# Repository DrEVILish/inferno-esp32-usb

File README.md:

# inferno-esp32-usb

Fixed-function 32×32 audio bridge: Inferno-compatible AoIP on RJ45 ↔ USB Audio Class 2.0 on USB-C. One ESP32-P4, no settings, boots and runs.

- **Network side:** AoIP device speaking the Dante-compatible protocol as implemented by [Inferno](https://github.com/teodly/inferno). 32 transmit + 32 receive channels, 48 kHz, 24-bit.
- **USB side:** class-compliant USB Audio Class 2.0 device. 32 playback + 32 capture channels, 48 kHz, High-Speed asynchronous with explicit feedback.
- **Mapping (fixed 1:1):** USB playback N → network TX N, network RX N → USB capture N.
- **Operation:** no configuration UI. Boots on USB-C bus power and runs (PoE deferred).

Target SoC: **ESP32-P4** — the only ESP32 with High-Speed USB (32×32 needs it; the S3's Full-Speed port tops out around 2–4 channels) plus an Ethernet MAC with IEEE 1588 hardware timestamps.

> Status: firmware for milestones M1–M5 is written but **not yet run on hardware** (2026-10-13). Until the bench matrix (docs/20/21) has passed, USB enumeration/throughput, Ethernet/PTP behaviour and the real-time figures quoted in the docs are **claims, not measurements** — do not rely on them. Next steps are bench order, own board, and open questions in `docs/30-roadmap.md`. Not affiliated with or endorsed by any AoIP protocol vendor.

**Threat model:** this is a dissector of an unauthenticated Dante-class
protocol on a LAN. The control plane (ARC/CMC/flow-control, ports 4440/8800/4455)
and info multicast accept any host: basic sanity (destination checks,
rate limits, name validation) is enforced, and abuse is counted in telemetry
(`aoip_info_drops`, `ptp_hw_*`, …), but there is no authentication — as with
Dante/Inferno itself. A hostile host on the same segment can re-route RX
channels, rename every channel, create or stop TX flows, and keep the
control task busy; info multicast is bounded by a token bucket and
degraded-startup state is visible in telemetry (`aoip_start_degraded`).
Assign it a port on a managed switch with ACLs / IGMP snooping, never a
flat, hostile network; if hostile LANs are actually in scope, an
authentication layer would have to be added on top (protocol-divergent).

Dev board: **Waveshare ESP32-P4-ETH** (RJ45/IP101; HS USB OTG on its 4-pin header → USB-C pigtail).

## Repo layout

| path | what |
|---|---|
| `firmware/` | ESP-IDF v6.1 firmware (C). See table below |
| `docs/` | Design notes, bench procedure, roadmap. See index below |
| `hardware/` | Own rev-1 board: SKiDL schematic-as-code → KiCad PCB (placement done, not routed) |
| `tools/` | Build scripts, host test/probe tools, simulations, host test runner |
| `patches/` | `esp_eth-rx64.patch`: raises IDF v6.1 EMAC RX ring cap 30 → 64 |
| `third_party/` | **Reference clones, study only, never committed** (see `.gitignore`): `inferno-esp32-p4` (8-ch RX-only prior art) and `inferno-upstream` (protocol reference) |
| `CHANGELOG.md` | Change log of the post-import work (releases 0.1.0/0.1.1) |

## Firmware

`firmware/` (ESP-IDF v6.1, C, GPL-3.0-or-later):

| part | files | doc |
|---|---|---|
| shared rings, config, telemetry | `main/audio`, `main/app_config.h`, `main/sys` | `docs/01-architecture.md` |
| Ethernet fast path, 1588 media clock, PTPv1 follower | `main/net`, `main/clock` | `docs/11-net-clock.md` |
| USB Audio 2.0, 32×32 HS async, own class driver on TinyUSB | `main/usb` | `docs/10-usb.md` |
| AoIP (Inferno-compatible): mDNS, ARC, CMC, info, flows TX/RX, subscriptions | `main/aoip` | `docs/12-aoip.md` |

Design details: single 1588 time base slaved to the PTPv1 leader; media clock derived arithmetically (no ASRC, bit-transparent). Network TX is 4×8-channel flows; USB uses 896-byte packets (6+1 frames) with a 4-byte feedback endpoint every 1 ms. IDF's `esp_eth` is overridden locally (`firmware/components/esp_eth` + `patches/` + `tools/esp_eth_override.sh`) for a 64-descriptor RX ring and hold-not-flush DMA behavior.

## Docs index

| doc | contents |
|---|---|
| `docs/00-plan.md` | Goal, starting points, milestones M0–M8, risks, open questions |
| `docs/01-architecture.md` | System design: clock architecture, bandwidth budgets |
| `docs/10-usb.md` | UAC2 32×32 HS async driver, descriptors, feedback engine, sim results |
| `docs/11-net-clock.md` | EMAC fast path, 1588 media clock, PTPv1 follower + servo |
| `docs/12-aoip.md` | AoIP module: ports, flows, subscriptions, NVS persistence |
| `docs/13-review-2026-10-13.md` | Cross-module review fixes (IRAM, NVS, rings, latency profiles) |
| `docs/14-latency.md` | Latency budget and profiles (10/6/4/2 ms) |
| `docs/15-profile.md` | Performance instrumentation, hot-path probes, gated optimization backlog |
| `docs/20-bench-testing.md` | Bench setup and test sequence (M1–M8) |
| `docs/21-latency-matrix.md` | Round-trip test matrix: 10/6/4/2 ms × 32/16/8/4/2 ch, modes A/B/C |
| `docs/30-roadmap.md` | Roadmap: no-HW phase, bench order, own board, release |
| `docs/40-board-rev1.md` | Own board rev 1: rationale, values, pins, power, risks |

## Hardware

`hardware/` holds the custom rev-1 board: USB-C (UAC2 HS, bus-powered) + RJ45 (10/100 RMII) on an ESP32-P4NRW32X, SKiDL schematic (`usb_inferno.py`) generating the KiCad netlist, BOM (`bom.csv`), and placed-but-unrouted 4-layer PCB. Full story in `hardware/README.md` and `docs/40-board-rev1.md`. Regenerate with `hardware/build.sh` (needs KiCad 9 + SKiDL venv); once human routing starts, stop regenerating the PCB and import netlist changes in pcbnew instead.

## Build

Prerequisites: ESP-IDF v6.1 with tools installed. `tools/idf-env.sh` sources it from `/opt/toolchain` — adjust the paths there if your IDF lives elsewhere.

```sh
tools/build.sh                         # production build (ends with check_iram.py)
tools/build-variant.sh USB_LOOPBACK    # bench variants: USB_LOOPBACK | NET_LOOPBACK | TONE
tools/build-matrix.sh                  # latency/channel test images (see docs/21-latency-matrix.md)
```

Every build ends with `tools/check_iram.py`: everything the USB interrupt can reach must be IRAM-resident (flash writes disable the cache). A failure fails the build.

Flash (example): `. tools/idf-env.sh && cd firmware && idf.py -p /dev/ttyACM0 flash`.

## Bench testing

Firmware written ≠ firmware proven. Start at `docs/20-bench-testing.md`: Waveshare board + managed switch with a Dante leader + Inferno on Linux, USB HS pigtail, telemetry over UDP (port 7779 via `tools/net_stats.py`).

| tool | purpose |
|---|---|
| `tools/build-variant.sh`, `tools/build-matrix.sh` | test images (loopback/tone, latency×channel matrix) |
| `tools/usb_loopback_test.py`, `tools/usb_descriptor_check.py` | M1: enumeration, 896 B packets, bit-exact OUT→IN |
| `tools/net_stats.py` | UDP telemetry receiver |
| `tools/aoip_probe.py`, `tools/aoip_pcap.py` | M3–M5: discovery/control probing, packet capture analysis |
| `tools/usb_engine_sim.sh`, `tools/ptp_servo_sim.c` | host-side simulations (feedback engine, servo) |
| `tools/latency_matrix.py` | latency model behind `docs/14` and `docs/21` |
| `tools/host_tests.sh` | run every host test (fpp select, perf windows, ts split, group bitmap, fork-comparable ARC/info replies) |

## Attribution and license

- Protocol reference: [teodly/inferno](https://github.com/teodly/inferno) (Rust, GPL-3.0+/AGPL-3.0+).
- Prior art consulted: `Nickster90s/Inferno-ESP32-P4` (8-ch receive-only; **no licence file — study material only**). It lives under `third_party/` and is excluded from version control by `.gitignore`, as is `third_party/inferno-upstream`.
- Firmware in this repo is written as GPL-3.0-or-later (see `tools/check_iram.py` SPDX header and `firmware/` notes). There is not yet a top-level `LICENSE` file; adding the GPL-3.0-or-later text is an open release task (Phase D in `docs/30-roadmap.md`).
- This project is not affiliated with or endorsed by any AoIP protocol vendor.

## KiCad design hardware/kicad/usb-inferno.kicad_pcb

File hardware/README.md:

# usb-inferno hardware (rev 1)

This folder holds the custom board: USB-C (UAC2 HS, bus powered) and RJ45 (10/100
RMII) on an ESP32-P4NRW32X. The design rationale, the sources of every value, the pin
table, the power budget and the risk list are in
[`docs/40-board-rev1.md`](../docs/40-board-rev1.md).

## Layout

| path | what | generated by |
|---|---|---|
| `usb_inferno.py` | **the schematic** (SKiDL). Every part, net and BOM field | hand-written |
| `lib/gen_lib.py` | custom symbols and footprint: ESP32-P4NRW32X (QFN104), IP101GRI, TPS25200DRV | hand-written |
| `lib/usb_inferno.kicad_sym`, `lib/usb_inferno.pretty/` | KiCad library used by the netlist and the PCB | `lib/gen_lib.py` |
| `kicad/usb-inferno.net` | KiCad netlist | `usb_inferno.py` |
| `bom.csv` | grouped BOM (ref, value, description, MPN, manufacturer, LCSC, LCSC status, footprint, qty, DNP) | `usb_inferno.py` |
| `erc.log` | SKiDL ERC result | `build.sh` |
| `kicad/usb-inferno.kicad_pcb` | 4-layer board: outline, stackup, placed parts, GND/3V3 zones, not routed | `tools/make_pcb.py` |
| `kicad/usb-inferno.kicad_pro`, `.kicad_dru` | net classes and patterns, JLC minimums, custom diff-pair/length rules | `tools/make_pcb.py` |
| `kicad/drc-unrouted.rpt` | `kicad-cli pcb drc` of the unrouted board | `build.sh` |
| `tools/pin_table.py` | prints the U1/U6 pin tables in docs/40 §5 from the netlist | — |

## Regenerate (netlist → PCB)

```sh
# one-time setup (Debian 13): KiCad 9 + libraries, SKiDL in a venv
nice apt-get install -y --no-install-recommends kicad kicad-symbols kicad-footprints
python3 -m venv /opt/usb-inferno/work/venv-hw && /opt/usb-inferno/work/venv-hw/bin/pip install skidl
# KiCad global library tables (normally created by KiCad's first-run wizard):
mkdir -p ~/.config/kicad/9.0 && cp -n /usr/share/kicad/template/*-lib-table ~/.config/kicad/9.0/

hardware/build.sh        # gen_lib -> SKiDL (ERC, netlist, BOM) -> pcbnew placement -> DRC
```

`tools/make_pcb.py` **overwrites** `usb-inferno.kicad_pcb`. Once the human layout pass
starts, stop running it. Push schematic changes into the routed board with
pcbnew *File → Import Netlist* (`kicad/usb-inferno.net`, match by reference).

## Status

- **ERC (SKiDL):** 0 errors, 0 warnings. SKiDL emits a netlist, not a `.kicad_sch`, so
  KiCad's schematic ERC does not apply. The remaining "fp-lib-table not found"
  messages come from SKiDL probing for KiCad 6/7/8/10 configurations and are harmless.
- **PCB DRC (unrouted):** 0 clearance, courtyard or edge errors. All violations left
  are expected for an unrouted board: unconnected items, silk overlaps of the staged
  passives, and the REF_CLK length rule (no tracks yet).
- **Routing: not started.** See docs/40 §18 for the list of what remains.

## Verified vs assumed

Verified against a cited document during this pass:
- P4 pins, power domains, rail ranges, decoupling, the v3.x pin 54 / DCDC / DP
  changes, strapping, CHIP_PU timing, flash voltage, crystal ([DS], [HDG], [REV3], [PCN]).
- IP101GRI pinout, package (QFN32 **4×4**), straps, 50 MHz-input mode, centre-tap
  handling, reset timing ([IP]); [WS] wiring for the same PHY.
- TPS25200, TLV62569 and TPD2EUSB30 pinouts and key values (TI data sheets).
- LCSC numbers marked `checked` in `bom.csv`.

Assumed or UNVERIFIED (details in docs/40 §17):
- the QFN104 land pattern (derived from the package drawing, not an Espressif
  footprint);
- stackup thicknesses and impedance geometry (closed-form models, not the JLC
  calculator);
- ESP32-P4NRW32X availability at LCSC/JLC (none found);
- LCSC numbers marked `recall`/`TBD`;
- HR911105A LED polarity (taken from the KiCad symbol);
- current estimates beyond the datasheet figures.

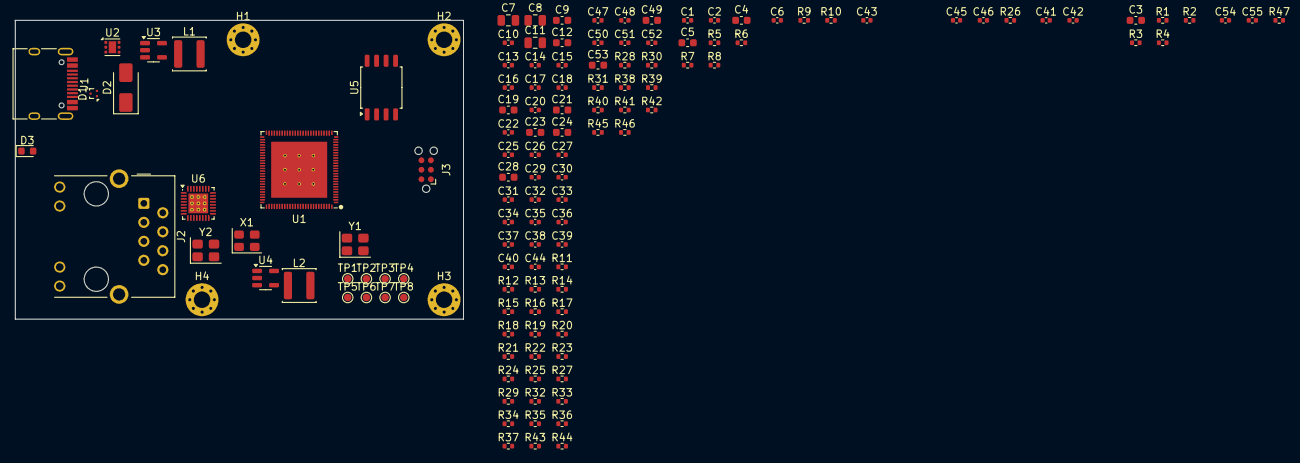
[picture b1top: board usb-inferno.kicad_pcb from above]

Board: 4 copper layers, 60.0 x 40.0 mm, 131 parts (0 on the bottom side), 83 nets, no tracks yet.

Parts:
C1, C33, C35, C38, C39, C40, C46: 1u; C_0402_1005Metric
C2, C13, C14, C15, C16, C17, C18, C20, C22, C25, C27, C29, C30, C31, C32, C34, C36, C37, C44, C45, C50, C51, C52, C54, C55: 100n; C_0402_1005Metric
C3: 10n; C_0603_1608Metric
C4, C12, C19, C21, C23, C24, C49, C53: 10u; C_0603_1608Metric
C5, C9, C28: 4.7u; C_0603_1608Metric
C6, C43: 22p DNP; C_0402_1005Metric
C7, C8, C11: 22u; C_0805_2012Metric
C10, C41, C42: 22p; C_0402_1005Metric
C26: 10n; C_0402_1005Metric
C47, C48: 20p DNP; C_0402_1005Metric
D1: TPD2EUSB30; Texas_DRT-3
D2: SMAJ5.0A; D_SMA
D3: green; LED_0603_1608Metric
H1, H2, H3, H4: M2; MountingHole_2.2mm_M2_Pad_Via
J1: USB-C; USB_C_Receptacle_HRO_TYPE-C-31-M-12
J2: RJ45; RJ45_Hanrun_HR911105A_Horizontal
J3: TC2030; Tag-Connect_TC2030-IDC-NL_2x03_P1.27mm_Vertical
L1, L2: 2.2u; L_Changjiang_FNR4020S
R1, R2, R38, R39, R40, R41, R42: 5.1k; R_0402_1005Metric
R3: 1M; R_0402_1005Metric
R4: 0 DNP; R_0402_1005Metric
R5, R6, R9: 100k; R_0402_1005Metric
R7: 150k; R_0402_1005Metric
R8, R15, R19, R23, R24, R44: 10k; R_0402_1005Metric
R10: 22k; R_0402_1005Metric
R11, R12: 499k; R_0402_1005Metric
R13, R14, R16, R17, R18, R20, R21, R26, R29, R30: 0; R_0402_1005Metric
R22: 1M DNP; R_0402_1005Metric
R25, R46, R47: 1k; R_0402_1005Metric
R27, R28, R32, R33, R34, R35, R36, R37: 22; R_0402_1005Metric
R31: 22 DNP; R_0402_1005Metric
R43: 1.5k; R_0402_1005Metric
R45: 6.19k; R_0402_1005Metric
TP1: USJ_D+; TestPoint_Pad_D1.0mm
TP2: USJ_D-; TestPoint_Pad_D1.0mm
TP3: 5V; TestPoint_Pad_D1.0mm
TP4: 3V3; TestPoint_Pad_D1.0mm
TP5: VDD_HP; TestPoint_Pad_D1.0mm
TP6: GND; TestPoint_Pad_D1.0mm
TP7: FAULT; TestPoint_Pad_D1.0mm
TP8: IO36; TestPoint_Pad_D1.0mm
U1: ESP32-P4NRW32X; Espressif_QFN-104-1EP_10x10mm_P0.35mm_EP7.5x7.5mm
U2: TPS25200DRV; WSON-6-1EP_2x2mm_P0.65mm_EP1x1.6mm
U3, U4: TLV62569DBV; SOT-23-5
U5: W25Q128JVS; SOIC-8_5.3x5.3mm_P1.27mm
U6: IP101GRI; QFN-32-1EP_4x4mm_P0.4mm_EP2.65x2.65mm_ThermalVias
X1: 50MHz; Oscillator_SMD_Abracon_ASE-4Pin_3.2x2.5mm
Y1: 40MHz; Crystal_SMD_3225-4Pin_3.2x2.5mm
Y2: 25MHz DNP; Crystal_SMD_3225-4Pin_3.2x2.5mm

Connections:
+3V3: C6.1, C7.1, C8.1, C9.1, C13.1, C14.1, C15.1, C16.1, C17.1, C18.1, C19.1, C20.1, C21.1, C22.1, C23.1, J3.1, L1.2, R8.2, R9.1, R13.1, R14.1, R15.1, R23.1, R24.1, R29.1, TP4.1, U1.9, U1.21, U1.62, U1.75, U1.77, U1.85, U1.96, U1.101, U4.4
CC1: J1.A5, R1.1
CC2: J1.B5, R2.1
CHASSIS: C3.1, H1.1, H2.1, H3.1, H4.1, J1.S1, J2.8, J2.SH, R3.1, R4.1
CHIP_PU: C40.1, J3.2, R15.2, U1.103
EFUSE_EN: R5.2, R6.1, U2.4
EFUSE_FAULT_N: R8.1, TP7.1, U2.3
EFUSE_ILIM: R7.1, U2.2
EN_DCDC: U1.79, U4.1
FB_3V3: C6.2, R9.2, R10.1, U3.5
FB_DCDC: C10.2, R11.2, R12.1, U1.78, U4.5
FLASH_CK: C43.1, R18.2, U5.6
FLASH_CK_P4: R18.1, U1.32
FLASH_CS: R19.2, U1.27, U5.1
FLASH_D: U1.33, U5.5
FLASH_HOLD: U1.31, U5.7
FLASH_Q: U1.28, U5.2
FLASH_WP: U1.29, U5.3
GND: C1.2, C2.2, C3.2, C4.2, C5.2, C7.2, C8.2, C9.2, C11.2, C12.2, C13.2, C14.2, C15.2, C16.2, C17.2, C18.2, C19.2, C20.2, C21.2, C22.2, C23.2, C24.2, C25.2, C26.2, C27.2, C28.2, C29.2, C30.2, C31.2, C32.2, C33.2, C34.2, C35.2, C36.2, C37.2, C38.2, C39.2, C40.2, C41.2, C42.2, C43.2, C44.2, C45.2, C46.2, C47.2, C48.2, C49.2, C50.2, C51.2, C52.2, C53.2, C54.2, C55.2, D1.3, D2.2, D3.1, J1.A1, J1.A12, J1.B1, J1.B12, J3.3, R1.2, R2.2, R3.2, R4.2, R6.2, R7.2, R10.2, R12.2, R22.2, R30.2, R38.2, R42.2, R44.2, R45.2, R47.2, TP6.1, U1.105, U2.5, U2.7, U3.2, U4.2, U5.4, U6.6, U6.7, U6.33, X1.2, Y1.2, Y1.4, Y2.2, Y2.4
GPIO36: R24.2, TP8.1, U1.68
LED_STATUS: R25.1, U1.22
LED_STATUS_A: D3.2, R25.2
MAG_LEDG_K: J2.10, R47.1
MAG_LEDY_K: J2.11, R46.1
MAG_RCT: C55.1, J2.5
MAG_TCT: C54.1, J2.4
MDC: U1.61, U6.22
MDIO: R43.2, U1.95, U6.23
MDI_RN: J2.6, U6.26
MDI_RP: J2.3, U6.27
MDI_TN: J2.2, U6.29
MDI_TP: J2.1, U6.30
OSC50_OUT: R27.1, R28.1, R31.2, X1.3
OSC50_VDD: C45.1, C46.1, R26.2, X1.1, X1.4
PHY_3V3: C51.1, C52.1, C53.1, J2.12, R26.1, R29.2, R39.1, R40.1, R41.1, R43.1, U6.13, U6.31
PHY_50M_CLKO: R31.1, U6.14
PHY_COL_RMII: R39.2, U6.4
PHY_CRS_DV: R37.1, U6.19
PHY_ISET: R45.1, U6.25
PHY_LED0_AD0: R41.2, R46.2, U6.11
PHY_LED3_AD3: J2.9, R42.1, U6.12
PHY_LEDMOD: R40.2, U6.20
PHY_REGOUT: C49.1, C50.1, U6.28
PHY_RST_N: R44.1, U1.94, U6.32
PHY_RXD0: R35.1, U6.18
PHY_RXD1: R36.1, U6.17
PHY_TXD0: R33.2, U6.9
PHY_TXD1: R34.2, U6.8
PHY_TXEN: R32.2, U6.5
PHY_TXER: R38.1, U6.1
PHY_X1: C47.1, R30.1, U6.2, Y2.1
PHY_X2: C48.1, U6.3, Y2.3
REF_CLK_MAC: R27.2, U1.93
REF_CLK_PHY: R28.2, U6.10
RMII_CRS_DV: R37.2, U1.57
RMII_RXD0: R35.2, U1.58
RMII_RXD1: R36.2, U1.60
RMII_TXD0: R33.1, U1.65
RMII_TXD1: J3.6, R23.2, R34.1, U1.66
RMII_TX_EN: R32.1, U1.92
SW_3V3: L1.1, U3.3
SW_HP: L2.1, U4.3
U0RXD: J3.5, U1.70
U0TXD: J3.4, U1.69
USB_CONN_D+: D1.1, J1.A6, J1.B6, R20.1
USB_CONN_D-: D1.2, J1.A7, J1.B7, R21.1
USB_D+: R20.2, R22.1, U1.50
USB_D-: R21.2, U1.49
USJ_DM: TP2.1, U1.52
USJ_DP: TP1.1, U1.53
VBUS_5V: C4.1, C5.1, TP3.1, U2.1, U3.1, U3.4
VBUS_C: C1.1, C2.1, D2.1, J1.A4, J1.A9, J1.B4, J1.B9, R5.1, U2.6
VDDO_3: C38.1, U1.73
VDDO_4: C39.1, U1.74
VDDO_FLASH: C33.1, C34.1, C44.1, R19.1, U1.30, U1.71, U5.8
VDDO_PSRAM: C35.1, C36.1, C37.1, U1.59, U1.67, U1.72
VDD_BAT: C24.1, C25.1, R13.2, U1.102
VDD_HP: C10.1, C11.1, C12.1, C29.1, C30.1, C31.1, C32.1, L2.2, R11.1, TP5.1, U1.26, U1.54, U1.76, U1.91
VDD_USBPHY: C26.1, C27.1, C28.1, R14.2, U1.51
XTAL_IN: C41.1, R16.2, Y1.1
XTAL_N: R17.1, U1.99
XTAL_OUT: C42.1, R17.2, Y1.3
XTAL_P: R16.1, U1.100

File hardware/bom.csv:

ref,value,description,MPN,manufacturer,LCSC,LCSC_status,footprint,qty,dnp
C2 C13 C14 C15 C16 C17 C18 C20 C22 C25 C27 C29 C30 C31 C32 C34 C36 C37 C44 C45 C50 C51 C52 C54 C55,100n,100nF 16V X7R 0402,CL05B104KO5NNNC,Samsung,C1525,recall,Capacitor_SMD:C_0402_1005Metric,25,
C3,10n,10nF 100V X7R 0603 (chassis bleed),CL10B103KC8NNNC,Samsung,C1589,recall,Capacitor_SMD:C_0603_1608Metric,1,
C26,10n,10nF 50V X7R 0402,CL05B103KB5NNNC,Samsung,C15195,recall,Capacitor_SMD:C_0402_1005Metric,1,
C4 C12 C19 C21 C23 C24 C49 C53,10u,10uF 10V X5R 0603,CL10A106KP8NNNC,Samsung,C19702,recall,Capacitor_SMD:C_0603_1608Metric,8,
C1 C33 C35 C38 C39 C40 C46,1u,1uF 25V X5R 0402,CL05A105KA5NQNC,Samsung,C52923,recall,Capacitor_SMD:C_0402_1005Metric,7,
C47 C48,20p DNP,20pF 50V C0G 0402,0402CG200J500NT,FH,C1554,recall,Capacitor_SMD:C_0402_1005Metric,2,DNP
C10 C41 C42,22p,22pF 50V C0G 0402,0402CG220J500NT,FH,C1555,recall,Capacitor_SMD:C_0402_1005Metric,3,
C6 C43,22p DNP,22pF 50V C0G 0402,0402CG220J500NT,FH,C1555,recall,Capacitor_SMD:C_0402_1005Metric,2,DNP
C7 C8 C11,22u,22uF 25V X5R 0805,CL21A226MAQNNNE,Samsung,C45783,recall,Capacitor_SMD:C_0805_2012Metric,3,
C5 C9 C28,4.7u,4.7uF 16V X5R 0603,CL10A475KO8NNNC,Samsung,C19666,recall,Capacitor_SMD:C_0603_1608Metric,3,
D2,SMAJ5.0A,"TVS 5.0 V standoff, 400 W, SMA",SMAJ5.0A,Littelfuse,C83329,recall,Diode_SMD:D_SMA,1,
D1,TPD2EUSB30,"2-ch ESD for USB HS/SS, 0.7 pF",TPD2EUSB30DRTR,Texas Instruments,C97502,checked,Package_TO_SOT_SMD:Texas_DRT-3,1,
D3,green,LED green 0603,19-217/GHC-YR1S2/3T,Everlight,C72043,recall,LED_SMD:LED_0603_1608Metric,1,
J2,RJ45,RJ45 magjack 10/100 with LEDs,HR911105A,HanRun,C12074,checked,Connector_RJ:RJ45_Hanrun_HR911105A_Horizontal,1,
J1,USB-C,"USB-C receptacle 16P, USB 2.0, SMD/THT shell",TYPE-C-31-M-12,Korean Hroparts Elec,C165948,checked,Connector_USB:USB_C_Receptacle_HRO_TYPE-C-31-M-12,1,
L1 L2,2.2u,2.2uH 3.7A Isat 4x4mm,FNR4020S2R2MT,cjiang (Changjiang Microelectronics),C167825,checked,Inductor_SMD:L_Changjiang_FNR4020S,2,
R13 R14 R16 R17 R18 R20 R21 R26 R29 R30,0,0R 0402,0402WGF0000TCE,UNI-ROYAL,C17168,recall,Resistor_SMD:R_0402_1005Metric,10,
R4,0 DNP,0R 0402,0402WGF0000TCE,UNI-ROYAL,C17168,recall,Resistor_SMD:R_0402_1005Metric,1,DNP
R43,1.5k,1.5k 1% 0402,0402WGF1501TCE,UNI-ROYAL,C25867,recall,Resistor_SMD:R_0402_1005Metric,1,
R5 R6 R9,100k,100k 1% 0402,0402WGF1003TCE,UNI-ROYAL,C25741,recall,Resistor_SMD:R_0402_1005Metric,3,
R8 R15 R19 R23 R24 R44,10k,10k 1% 0402,0402WGF1002TCE,UNI-ROYAL,C25744,recall,Resistor_SMD:R_0402_1005Metric,6,
R7,150k,150k 1% 0402,0402WGF1503TCE,UNI-ROYAL,C25755,recall,Resistor_SMD:R_0402_1005Metric,1,
R3,1M,1M 1% 0402,0402WGF1004TCE,UNI-ROYAL,C26083,recall,Resistor_SMD:R_0402_1005Metric,1,
R22,1M DNP,1M 1% 0402,0402WGF1004TCE,UNI-ROYAL,C26083,recall,Resistor_SMD:R_0402_1005Metric,1,DNP
R25 R46 R47,1k,1k 1% 0402,0402WGF1001TCE,UNI-ROYAL,C11702,recall,Resistor_SMD:R_0402_1005Metric,3,
R27 R28 R32 R33 R34 R35 R36 R37,22,22R 1% 0402,0402WGF220JTCE,UNI-ROYAL,C25092,recall,Resistor_SMD:R_0402_1005Metric,8,
R31,22 DNP,22R 1% 0402,0402WGF220JTCE,UNI-ROYAL,C25092,recall,Resistor_SMD:R_0402_1005Metric,1,DNP
R10,22k,22k 1% 0402,0402WGF2202TCE,UNI-ROYAL,C25768,recall,Resistor_SMD:R_0402_1005Metric,1,
R11 R12,499k,"499k 1% 0402 (VDD_HP FB, [HDG] Fig. 5)",0402WGF4993TCE,UNI-ROYAL,,TBD,Resistor_SMD:R_0402_1005Metric,2,
R1 R2 R38 R39 R40 R41 R42,5.1k,5.1k 1% 0402,0402WGF5101TCE,UNI-ROYAL,C25905,recall,Resistor_SMD:R_0402_1005Metric,7,
R45,6.19k,6.19k 1% 0402 (IP101 ISET),0402WGF6191TCE,UNI-ROYAL,,TBD,Resistor_SMD:R_0402_1005Metric,1,
U1,ESP32-P4NRW32X,"ESP32-P4 rev v3.x, 32MB PSRAM in package, QFN104",ESP32-P4NRW32X,Espressif Systems,,TBD,usb_inferno:Espressif_QFN-104-1EP_10x10mm_P0.35mm_EP7.5x7.5mm,1,
U6,IP101GRI,10/100 Ethernet PHY RMII QFN32 4x4,IP101GRI,IC Plus,C703537,checked,Package_DFN_QFN:QFN-32-1EP_4x4mm_P0.4mm_EP2.65x2.65mm_ThermalVias,1,
U3 U4,TLV62569DBV,2A 1.5MHz sync buck,TLV62569DBVR,Texas Instruments,C141836,checked,Package_TO_SOT_SMD:SOT-23-5,2,
U2,TPS25200DRV,"5V eFuse 20V-tolerant, soft start, adj. current limit",TPS25200DRVR,Texas Instruments,C128401,checked,Package_SON:WSON-6-1EP_2x2mm_P0.65mm_EP1x1.6mm,1,
U5,W25Q128JVS,128Mbit QSPI NOR 3.3V SOIC-8 208mil,W25Q128JVSIQ,Winbond,C97521,checked,Package_SO:SOIC-8_5.3x5.3mm_P1.27mm,1,
X1,50MHz,50MHz CMOS XO 1.62-3.63V +-25ppm 3225 (clock option A; remove for B),ECS-3225MV-500-CN-TR,ECS Inc.,C405974,checked,Oscillator:Oscillator_SMD_Abracon_ASE-4Pin_3.2x2.5mm,1,
Y2,25MHz DNP,"25MHz 3225 crystal, PHY clock option B (fit for B)",X322525MSB4SI,YXC,C13740,checked,Crystal:Crystal_SMD_3225-4Pin_3.2x2.5mm,1,DNP
Y1,40MHz,40MHz 15pF +-10ppm 3225,X322540MPB4SI,YXC,C9010,checked,Crystal:Crystal_SMD_3225-4Pin_3.2x2.5mm,1,

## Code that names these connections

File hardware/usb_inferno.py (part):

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# --- USB-Serial-JTAG (FS, GPIO24 D-/GPIO25 D+) to test pads only [HDG 1.3.12]
USJ_DN, USJ_DP = Net("USJ_DM"), Net("USJ_DP")
P4("GPIO24").__iadd__(USJ_DN)
P4("GPIO25").__iadd__(USJ_DP)

# --- UART0 (GPIO37 TX, GPIO38 RX) [HDG 1.3.6] and straps
U0TXD, U0RXD = Net("U0TXD"), Net("U0RXD")
P4("GPIO37").__iadd__(U0TXD)
P4("GPIO38").__iadd__(U0RXD)
BOOT = Net("RMII_TXD1")            # GPIO35 = boot strap AND RMII TXD1
STRAP36 = Net("GPIO36")
P4("GPIO36").__iadd__(STRAP36)
R("10k", V3V3, BOOT, note="GPIO35 boot strap pull-up (=1 SPI boot) [HDG 1.3.8]")
R("10k", V3V3, STRAP36, note="GPIO36=1 so BOOT-low gives Joint Download [DS Table 3-3]")

# --- status LED (firmware-driven, active high)
LED_ST = Net("LED_STATUS")
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
# --- RMII to IP101GRI (pin map = firmware app_config.h, unchanged)
RMII = OrderedDict([
    ("GPIO28", "RMII_CRS_DV"), ("GPIO29", "RMII_RXD0"), ("GPIO30", "RMII_RXD1"),
    ("GPIO31", "MDC"), ("GPIO34", "RMII_TXD0"), ("GPIO49", "RMII_TX_EN"),
    ("GPIO50", "REF_CLK_MAC"), ("GPIO51", "PHY_RST_N"), ("GPIO52", "MDIO"),
])
RN = {v: Net(v) for v in RMII.values()}
RN["RMII_TXD1"] = BOOT
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P4("GPIO35").__iadd__(BOOT)

# every other GPIO unconnected
used = set(RMII) | {"GPIO35", "GPIO36", "GPIO37", "GPIO38", "GPIO24", "GPIO25", "GPIO20"}
for num, name in LIB_P4.items():
    if name.startswith("GPIO") and name not in used:
        U1[num] += NC
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R("0", PHY_3V3, OSC_VDD, note="osc supply (fit ferrite/10R if spurs)")
C("100n", OSC_VDD, note="osc decap")
C("1u", OSC_VDD, note="osc decap")
R("22", OSC_OUT, RN["REF_CLK_MAC"], note="REF_CLK to P4 GPIO50 [HDG 1.3.14 series R]")
R("22", OSC_OUT, REF_CLK_PHY, note="REF_CLK to PHY 50M_CLKI")

# ===========================================================================
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# --- RMII clock option, selected by population only (docs/40 7.2):
#  A (default): X1 50 MHz XO fitted, R "X1 to GND" fitted; Y2, its caps and R_CLKO DNP.
#  B (fallback, = [WS]/[EVX]): X1 XO removed, R "X1 to GND" removed; fit Y2 25 MHz + 2x20p
#    and R_CLKO 22R: PHY 50M_CLKO -> OSC50_OUT star -> 22R -> GPIO50 and 22R -> PHY 50M_CLKI.
R("0", PHY_X1, GND, note="CLK option A: X1 to GND (50 MHz into 50M_CLKI) [IP Table 3]; remove for B")
Y2 = part("Device", "Crystal_GND24", "Y2", "Crystal:Crystal_SMD_3225-4Pin_3.2x2.5mm",
          "X322525MSB4SI", "YXC", "C13740", "checked",
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# series 22R at the driver end of every RMII data line
R("22", RN["RMII_TX_EN"], PHY["PHY_TXEN"], note="at P4")
R("22", RN["RMII_TXD0"], PHY["PHY_TXD0"], note="at P4")
R("22", BOOT, PHY["PHY_TXD1"], note="at P4 (GPIO35 strap stays on P4 side)")
R("22", PHY["PHY_RXD0"], RN["RMII_RXD0"], note="at PHY")
R("22", PHY["PHY_RXD1"], RN["RMII_RXD1"], note="at PHY")
R("22", PHY["PHY_CRS_DV"], RN["RMII_CRS_DV"], note="at PHY")
# straps: 5.1 kΩ per [IP Table 12]
R("5.1k", PHY["PHY_TXER"], GND, note="TXER low in RMII [IP pin 1]")
R("5.1k", PHY_3V3, PHY["PHY_COL_RMII"], note="COL/RMII=1 -> RMII")
R("5.1k", PHY_3V3, PHY["PHY_LEDMOD"], note="LEDMOD=1 -> LED mode 2")
R("5.1k", PHY_3V3, PHY["PHY_LED0_AD0"], note="PHY_AD0=1 -> PHY address 1 (firmware)")
R("5.1k", PHY["PHY_LED3_AD3"], GND, note="PHY_AD3=0")
R("1.5k", PHY_3V3, RN["MDIO"], note="MDIO pull-up (WS R59)")
R("10k", RN["PHY_RST_N"], GND, note="hold PHY in reset until firmware releases it")
R("6.19k", PHY["PHY_ISET"], GND, note="ISET 6.19k 1% [IP pin 25]")
C("10u", PHY["PHY_REGOUT"], size="0603", note="REGOUT [IP pin 28]")
C("100n", PHY["PHY_REGOUT"], note="REGOUT")
C("100n", PHY_3V3, note="VDDIO")
C("100n", PHY_3V3, note="AVDD33")
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J3[4] += U0TXD
J3[5] += U0RXD
J3[6] += BOOT
for net, label in ((USJ_DP, "USJ_D+"), (USJ_DN, "USJ_D-"), (VBUS_5V, "5V"), (V3V3, "3V3"),
                   (VDD_HP, "VDD_HP"), (GND, "GND"), (EFUSE_FLT, "FAULT"), (STRAP36, "IO36")):
    tp = non_bom("Connector", "TestPoint", "TP", "TestPoint:TestPoint_Pad_D1.0mm", value=label)
    tp[1] += net
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

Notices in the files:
hardware/usb_inferno.py:
SPDX-License-Identifier: CERN-OHL-S-2.0
